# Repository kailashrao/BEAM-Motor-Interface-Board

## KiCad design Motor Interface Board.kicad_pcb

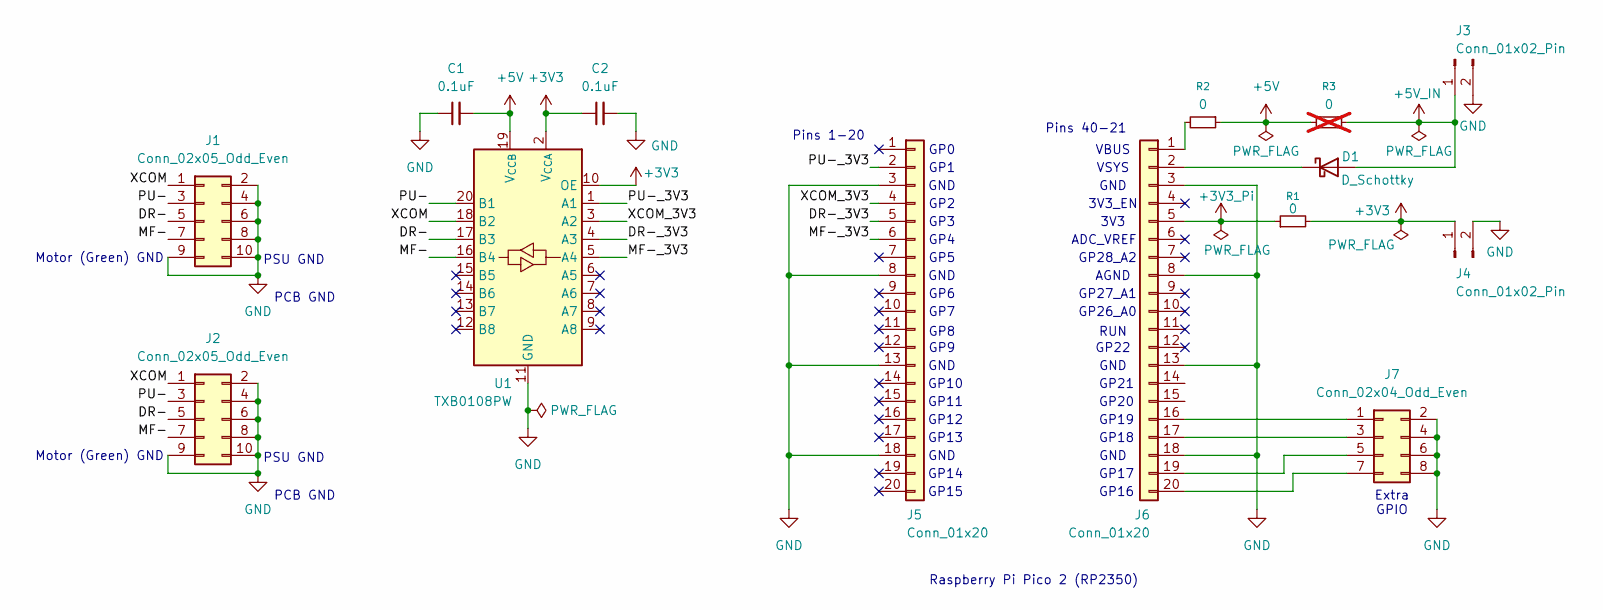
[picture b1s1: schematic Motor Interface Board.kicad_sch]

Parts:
C1, C2: 0.1uF; C_0805_2012Metric_Pad1.18x1.45mm_HandSolder
D1: D_Schottky; D_SMA_Handsoldering
J1, J2: Conn_02x05_Odd_Even; PinHeader_2x05_P2.54mm_Vertical
J3, J4: Conn_01x02_Pin; PinHeader_1x02_P2.54mm_Vertical
J5, J6: Conn_01x20; PinSocket_1x20_P2.54mm_Vertical
J7: Conn_02x04_Odd_Even; PinHeader_2x04_P2.54mm_Vertical
R1, R2: 0; R_0805_2012Metric_Pad1.20x1.40mm_HandSolder
R3: 0; R_0805_2012Metric_Pad1.20x1.40mm_HandSolder; not fitted
U1: TXB0108PW; TSSOP-20_4.4x6.5mm_P0.65mm

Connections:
+3V3: C2.1, J4.1, R1.2, U1.2 (V_{CCA}), U1.10 (OE)
+3V3_Pi: J6.5, R1.1
+5V: C1.2, R2.1, R3.2, U1.19 (V_{CCB})
+5V_IN: D1.2 (A), J3.1, R3.1
/DR-: J1.5, J2.5, U1.17 (B3)
/DR-_3V3: J5.5, U1.4 (A3)
/MF-: J1.7, J2.7, U1.16 (B4)
/MF-_3V3: J5.6, U1.5 (A4)
/PU-: J1.3, J2.3, U1.20 (B1)
/PU-_3V3: J5.2, U1.1 (A1)
/XCOM: J1.1, J2.1, U1.18 (B2)
/XCOM_3V3: J5.4, U1.3 (A2)
GND: C1.1, C2.2, J1.2, J1.4, J1.6, J1.8, J1.9, J1.10, J2.2, J2.4, J2.6, J2.8, J2.9, J2.10, J3.2, J4.2, J5.3, J5.8, J5.13, J5.18, J6.3, J6.8, J6.13, J6.18, J7.2, J7.4, J7.6, J7.8, U1.11 (GND)
unnamed: D1.1 (K), J6.2
unnamed: J6.1, R2.2
unnamed: J6.16, J7.1
unnamed: J6.17, J7.3
unnamed: J6.19, J7.5
unnamed: J6.20, J7.7

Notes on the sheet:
GP11
GP13
PCB GND
GP7
3V3
Motor (Green) GND
GP0
GP15
RUN
ADC_VREF
GP20
GP19
GP5
GP28_A2
GP4
GP14
Raspberry Pi Pico 2 (RP2350)
GP6
PSU GND
GND
GP9
Pins 1-20
GP1
GP18
VSYS
GP10
GP12
AGND
GP2
Pins 40-21
3V3_EN
GP17
GP3
GP16
GP26_A0
GP27_A1
Extra GPIO
GP22
VBUS
GP8

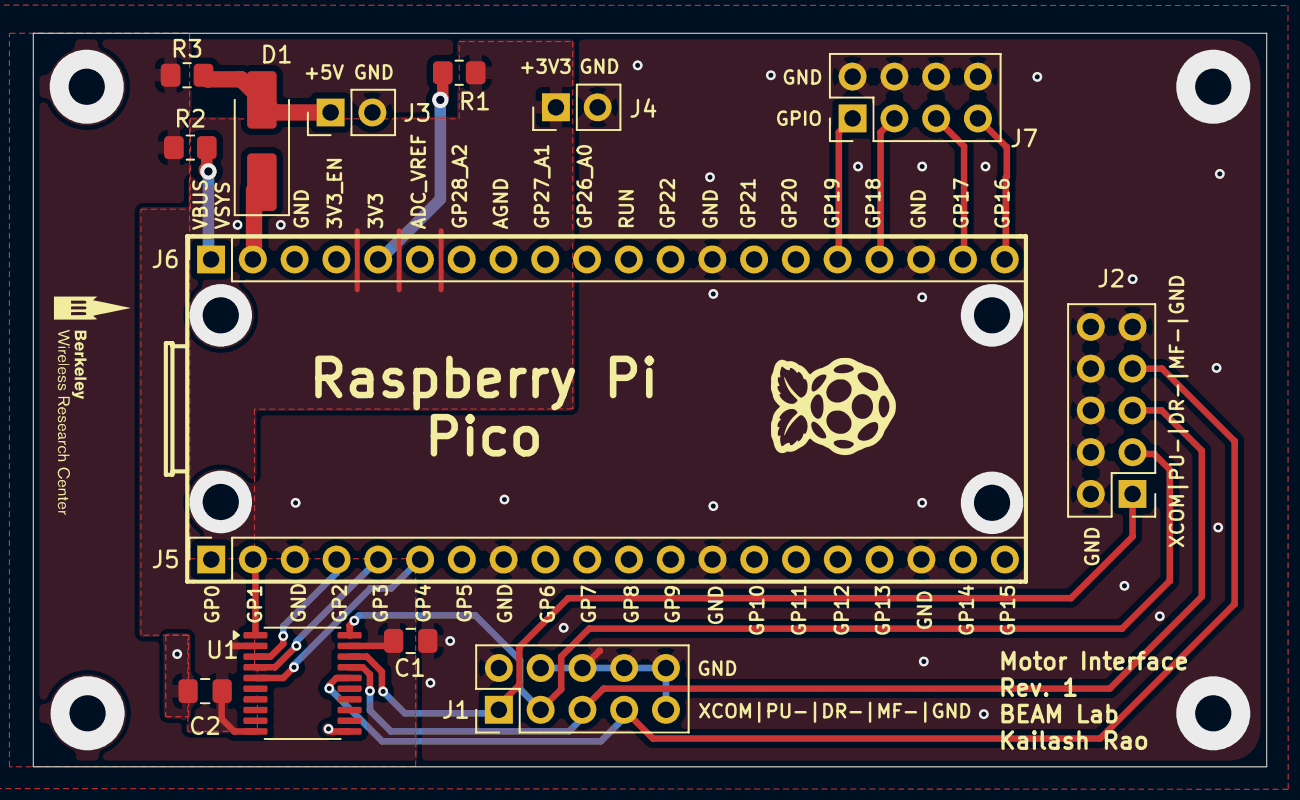
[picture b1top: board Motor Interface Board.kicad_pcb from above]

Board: 2 copper layers, 75.0 x 44.6 mm, 14 parts (0 on the bottom side), 19 nets.

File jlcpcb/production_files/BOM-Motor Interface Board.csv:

Comment,Designator,Footprint,LCSC,Quantity
0,"R1,R2",R_0805_2012Metric_Pad1.20x1.40mm_HandSolder,C96345,2
0.1uF,"C1,C2",C_0805_2012Metric_Pad1.18x1.45mm_HandSolder,C116837,2
Conn_01x02_Pin,"J3,J4",PinHeader_1x02_P2.54mm_Vertical,C32713268,2
Conn_01x20,"J5,J6",PinSocket_1x20_P2.54mm_Vertical,C7509519,2
Conn_02x04_Odd_Even,J7,PinHeader_2x04_P2.54mm_Vertical,C5156676,1
Conn_02x05_Odd_Even,"J1,J2",PinHeader_2x05_P2.54mm_Vertical,C42431818,2
D_Schottky,D1,D_SMA_Handsoldering,C83852,1
TXB0108PW,U1,TSSOP-20_4.4x6.5mm_P0.65mm,C53406,1

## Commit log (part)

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2026-06-17 Initial commit - schematic
2026-06-17 Update J1/J2 to be 2x5, route PU- through A1/B1 and GP1
2026-06-17 Source +5V from either VBUS or +5V_IN
2026-06-24 Layout placement
2026-06-24 Add mounting holes + reconfigure GPIO to use SPI capable pins
2026-06-24 Move J2 to right of pico
2026-06-25 Rotate J2, replace edge cut mounting holes with vias to ground
2026-06-29 Power pours + routing
2026-06-30 GND stitching vias
